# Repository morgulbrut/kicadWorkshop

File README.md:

## Getting the docs

See the Releases tab.

## Building the docs

Use [dotgo](https://github.com/morgulbrut/dotgo).

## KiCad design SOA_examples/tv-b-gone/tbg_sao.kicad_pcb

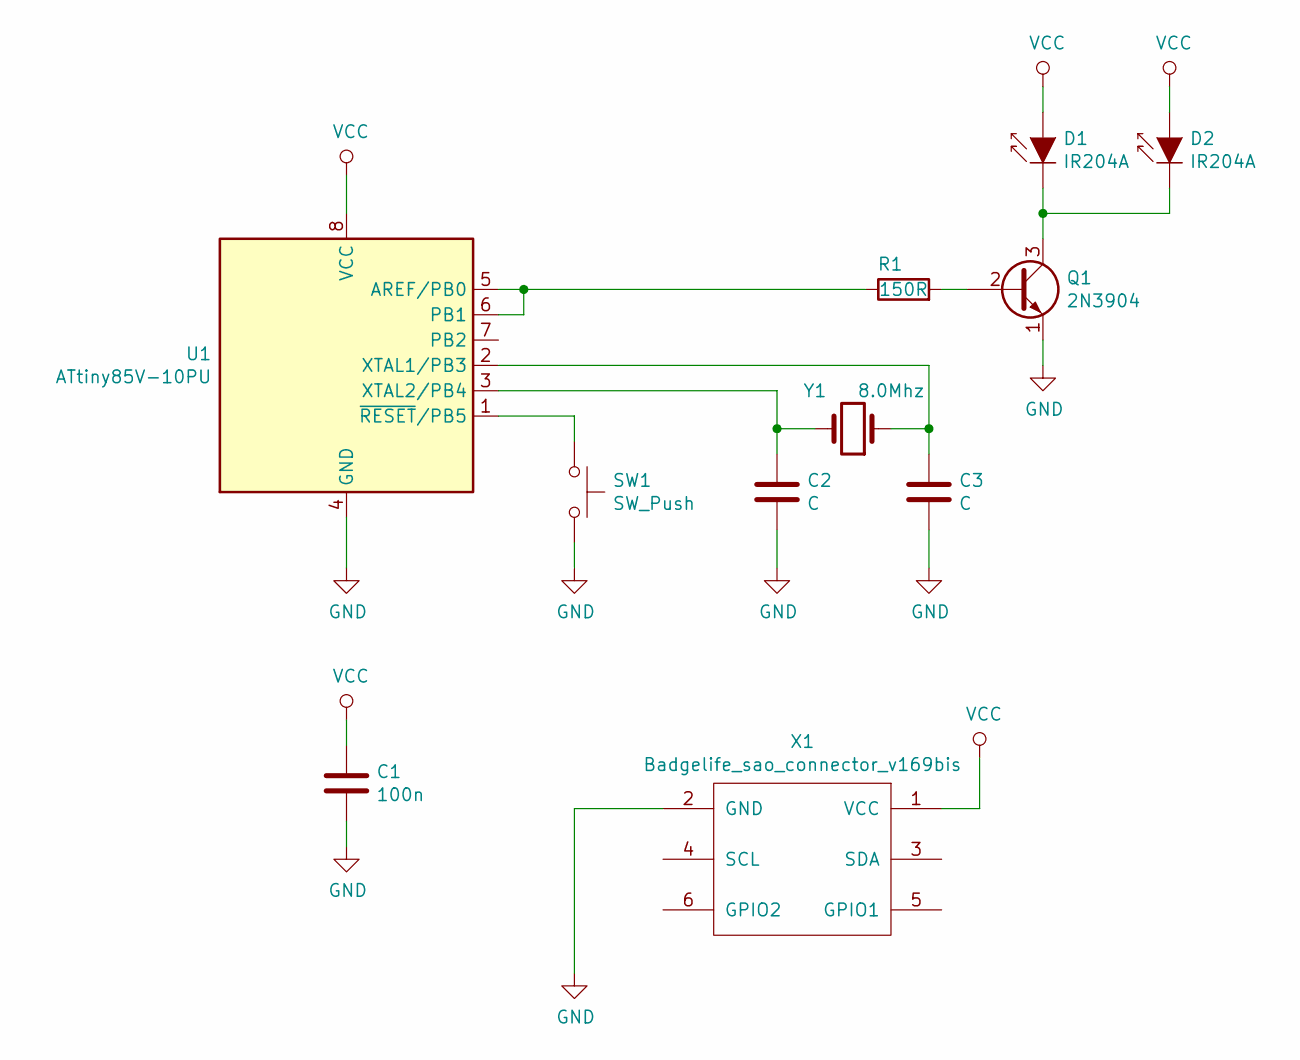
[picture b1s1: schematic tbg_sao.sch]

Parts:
C1: 100n; C_1206_3216Metric_Pad1.42x1.75mm_HandSolder
C2, C3: C; C_1206_3216Metric_Pad1.42x1.75mm_HandSolder
D1, D2: IR204A; LED_D5.0mm
Q1: 2N3904; TO-92_Inline
R1: 150R; R_1206_3216Metric_Pad1.42x1.75mm_HandSolder
SW1: SW_Push; SW_Push_1P1T_NO_6x6mm_H9.5mm
U1: ATtiny85V-10PU; DIP-8_W8.89mm_SMDSocket_LongPads
X1: Badgelife_sao_connector_v169bis; Badgelife-SAOv169-SAO-2x3
Y1: 8.0Mhz; Crystal_AT310_D3.0mm_L10.0mm_Vertical

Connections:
GND: C1.2, C2.2, C3.2, Q1.1 (E), SW1.2, U1.4 (GND), X1.2 (GND)
unnamed: C2.1, U1.3 (XTAL2/PB4), Y1.2
unnamed: C3.1, U1.2 (XTAL1/PB3), Y1.1
unnamed: D1.1 (K), D2.1 (K), Q1.3 (C)
unnamed: Q1.2 (B), R1.2
unnamed: R1.1, U1.5 (AREF/PB0), U1.6 (PB1)
unnamed: SW1.1, U1.1 (~RESET~/PB5)
VCC: C1.1, D1.2 (A), D2.2 (A), U1.8 (VCC), X1.1 (VCC)

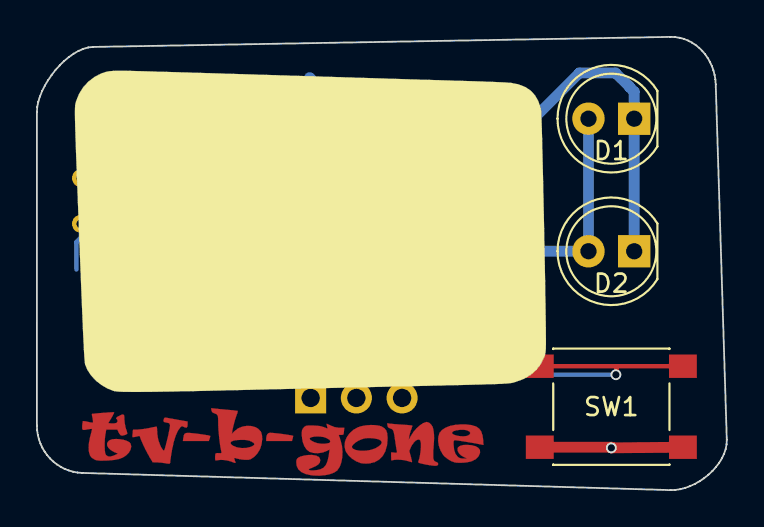
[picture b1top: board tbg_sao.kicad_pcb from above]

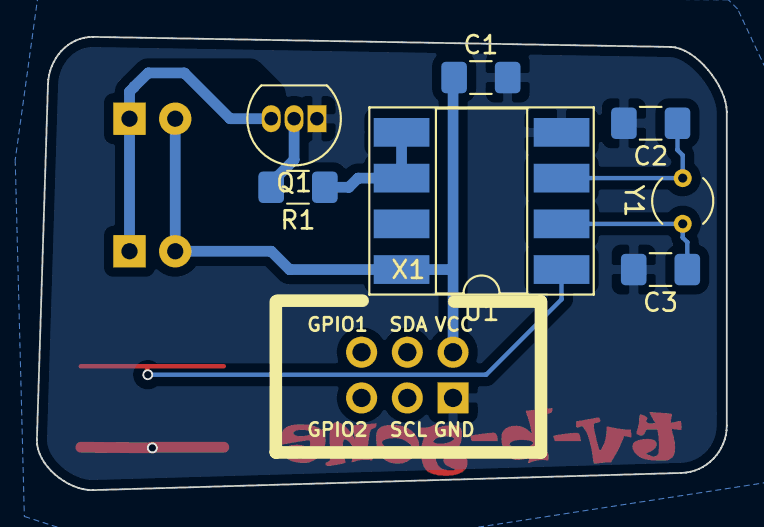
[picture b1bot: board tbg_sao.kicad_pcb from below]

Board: 2 copper layers, 38.3 x 25.2 mm, 11 parts (7 on the bottom side), 8 nets.

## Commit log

2019-02-05 Inital commit
2019-02-05 .gitignore
2019-02-05 README angepasst
2019-02-07 changed presentation
2019-02-07 Readme changed
2019-06-05 English
2019-06-20 Updated presentation
2019-06-20 Updated slides after CoSin
2020-01-16 SAO workshop inital
2020-01-21 Deleted unused files
2020-01-22 workflow chart added
2020-01-22 gitignore
2020-01-22 workflow as an image
2020-01-22 tv-b-gone example added
2020-01-22 cheese title slide added
2020-01-22 added cheesy gif
2020-01-23 removed workspace
2020-01-23 renamed readme
2020-01-23 gitignore update
2020-01-24 added link
2020-01-24 use menukeys LaTeX package
2020-01-27 Updated kicad stuff
2020-01-27 updated gitignore
2020-01-27 cleanded up shortcuts table
2020-01-27 added some troubleshooting hints for linux
2020-01-28 Readme added
2020-01-28 small improvements
2020-01-28 huge improvements
2020-01-28 moved the menukeys to header file
2020-01-28 added beamer header file
2020-01-28 updated config
2020-01-28 Styling
2020-01-28 umdated header
2020-01-28 title fonts fixed
2020-01-29 removed reveal.js
2020-01-29 beamer port
2020-01-29 fixed animation
2020-01-30 settings toml changed
2020-02-03 Cleanup
2020-02-03 Updated docu
2020-02-06 Ready for the workshop
2020-02-06 Added content
2020-02-07 Schedule added
2020-02-07 changed Layer suffix
2020-02-07 added a paragraph about SAO
2020-02-07 Rearranged stuff
2020-02-07 typos fixed
2020-02-07 fixed error in the flowchart
2020-02-07 fixed flowchart
2020-02-07 small fixes on the presentation
2020-02-07 flowchart
2020-02-09 blinky added
2020-02-09 Footprints fixed
2020-02-10 svg2shenzen issue 64
2020-03-10 added covid-19 sao
2020-03-10 finished pcb
